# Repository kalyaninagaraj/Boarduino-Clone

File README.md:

# Boarduino Clone 
&nbsp;&nbsp; <br />
This clone-of-a-clone is an adaptation of the breadboard and through-hole parts-friendly [Arduino Uno](https://store.arduino.cc/usa/arduino-uno-rev3), a.k.a. [Boarduino by Lady Ada](https://learn.adafruit.com/boarduino-kits). 

The orginal Boarduino was designed with a ceramic resonator in mind, which isn't available at my local electronics stores. So I redesigned the layout in [Autodesk EAGLE](https://www.autodesk.com/products/eagle) to make space for the more readily available crystal oscillator. 

## Final Product
Check out this [blinking LED demo](https://youtu.be/2WAObtuopfo) for a look at the final (manufactured and assembled) board. 

### A Note On The Microcontroller 
I could only manage to get my hands on a [ATMEGA328-PU](https://www.microchip.com/wwwproducts/en/ATMEGA328), and not the Arduino-supported [ATMEGA328P-PU](https://www.microchip.com/wwwproducts/en/ATMEGA328P), which means bootloading troubles! Of the handful of workarounds that I found on the web, [this one](http://www.crash-bang.com/resource/bootload-atmega328/) helped the most.  

## Resources
Here are links to the original Boarduino, other Boarduino-like products, and some related resources. 
1. [DC and USB Boarduino kits and assembly tutorial by Lada Ada, Adafruit Industries](https://learn.adafruit.com/boarduino-kits). 
2. [Really Bare Bones Board (RBBB) by Modern Device](https://moderndevice.com/product/rbbb-kit/). Their [document on assembly instructions](https://cdn.shopify.com/s/files/1/0038/9582/files/RBBB_Instructions_06.pdf?1260749296) includes a great how-to section for soldering novices.
3. If the purple PCB in the video wasn't enough of a hint, I got the boards fabricated from [OSH Park](https://oshpark.com/)! 

## Design Credit
[@kalyaninagaraj](https://github.com/kalyaninagaraj)

## Hardware License
The design files are made available under [CC BY-SA 3.0](https://creativecommons.org/licenses/by-sa/3.0/).

## Tags
#Open-Source Hardware #Arduino Uno Clone # Boarduino Clone #Adafruit

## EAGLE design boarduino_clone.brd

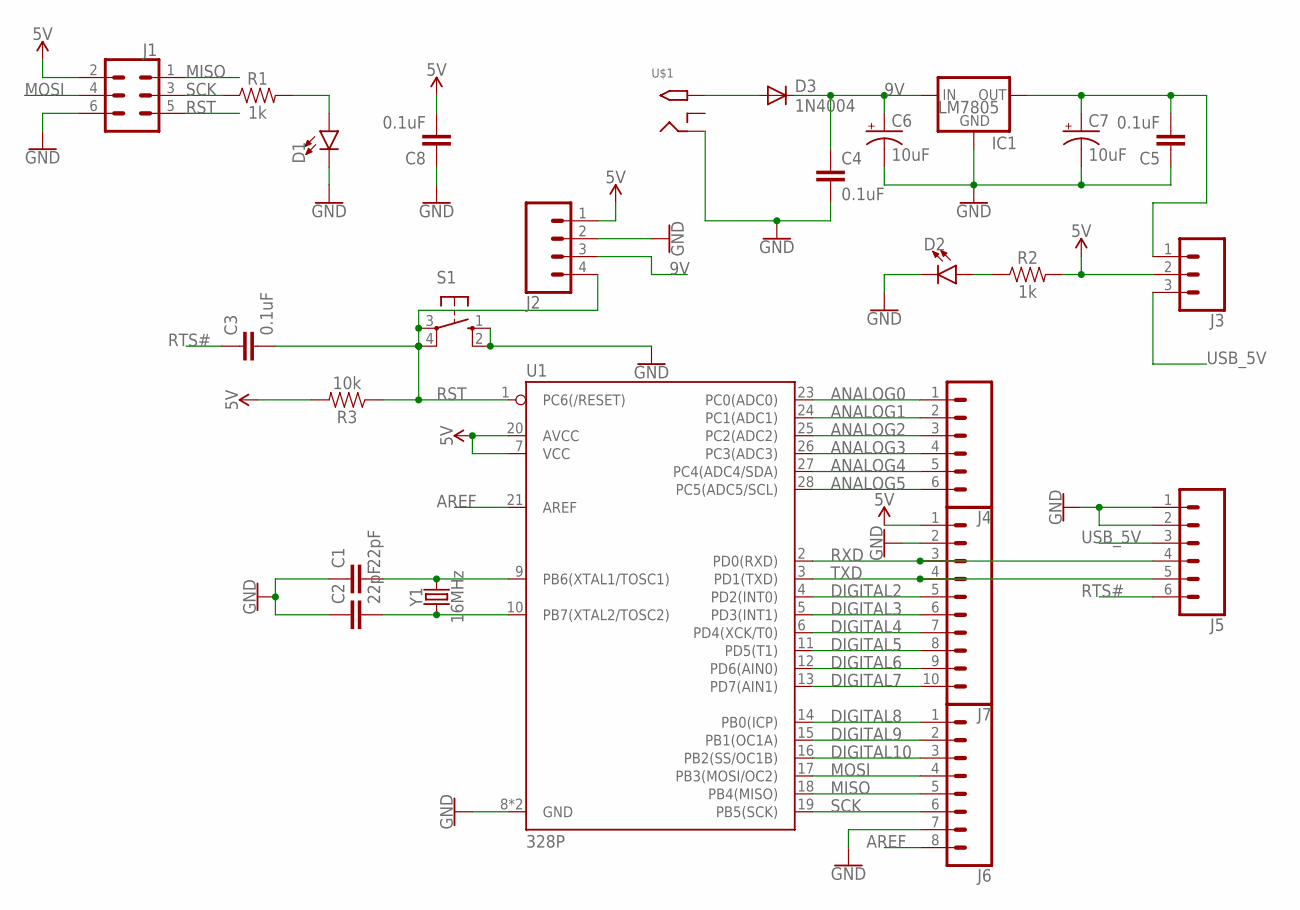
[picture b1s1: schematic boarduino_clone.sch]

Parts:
C1, C2: 22pF; CAP-PTH-2.54
C3, C4, C5, C8: 0.1uF; CAP-PTH-SMALL-KIT
C6, C7: 10uF; CPOL-RADIAL-2.5MM-5MM
D1, D2: LED5MM; LED_5MM
D3: 1N4004; DO41-10
IC1: LM7805; 78XXS
J1: FEMALE 2x3; 2X3
J2: CONN_041X04_NO_SILK; 1X04_NO_SILK
J3: CONN_031X03_NO_SILK; 1X03_NO_SILK
J4, J5: CONN_06NO_SILK_FEMALE_PTH; 1X06_NO_SILK
J6: CONN_08NO_SILK_FEMALE_PTH; 1X08_NO_SILK
J7: CONN_10NO_SILK_PTH_FEMALE; 1X10_NO_SILK
R1, R2: 1k; AXIAL-0.1
R3: 10k; AXIAL-0.1
S1: 10-XX; B3F-10XX
U1: 328P; DIP28
U$1: 2.1MMJACKTHM; PJ-102A
Y1: 16MHz; HC49US

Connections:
5V: C8.2, J1.2, J2.1, J3.2, J7.1, R2.P$2 (2), R3.P$2 (2), U1.7 (VCC), U1.20 (AVCC)
9V: C4.1, C6.1 (+), D3.C, IC1.IN, J2.3
ANALOG0: J4.1, U1.23 (PC0(ADC0))
ANALOG1: J4.2, U1.24 (PC1(ADC1))
ANALOG2: J4.3, U1.25 (PC2(ADC2))
ANALOG3: J4.4, U1.26 (PC3(ADC3))
ANALOG4: J4.5, U1.27 (PC4(ADC4/SDA))
ANALOG5: J4.6, U1.28 (PC5(ADC5/SCL))
AREF: J6.8, U1.21 (AREF)
DIGITAL2: J7.5, U1.4 (PD2(INT0))
DIGITAL3: J7.6, U1.5 (PD3(INT1))
DIGITAL4: J7.7, U1.6 (PD4(XCK/T0))
DIGITAL5: J7.8, U1.11 (PD5(T1))
DIGITAL6: J7.9, U1.12 (PD6(AIN0))
DIGITAL7: J7.10, U1.13 (PD7(AIN1))
DIGITAL8: J6.1, U1.14 (PB0(ICP))
DIGITAL9: J6.2, U1.15 (PB1(OC1A))
DIGITAL10: J6.3, U1.16 (PB2(SS/OC1B))
GND: C1.1, C2.1, C4.2, C5.1, C6.2 (-), C7.2 (-), C8.1, D1.K (C), D2.K (C), IC1.GND, J1.6, J2.2, J5.1, J5.2, J6.7, J7.2, S1.1 (S), S1.2 (S1), U1.8 (GND), U1.22 (GND), U$1.RING
MISO: J1.1, J6.5, U1.18 (PB4(MISO))
MOSI: J1.4, J6.4, U1.17 (PB3(MOSI/OC2))
unnamed: D1.A, R1.P$2 (2)
unnamed: C1.2, U1.9 (PB6(XTAL1/TOSC1)), Y1.2
unnamed: C2.2, U1.10 (PB7(XTAL2/TOSC2)), Y1.1
unnamed: D3.A, U$1.TIP
unnamed: C5.2, C7.1 (+), IC1.OUT, J3.1
unnamed: D2.A, R2.P$1 (1)
RST: C3.2, J1.5, J2.4, R3.P$1 (1), S1.3, S1.4 (P1), U1.1 (PC6(/RESET))
RTS#: C3.1, J5.6
RXD: J5.4, J7.3, U1.2 (PD0(RXD))
SCK: J1.3, J6.6, R1.P$1 (1), U1.19 (PB5(SCK))
TXD: J5.5, J7.4, U1.3 (PD1(TXD))
USB_5V: J3.3, J5.3

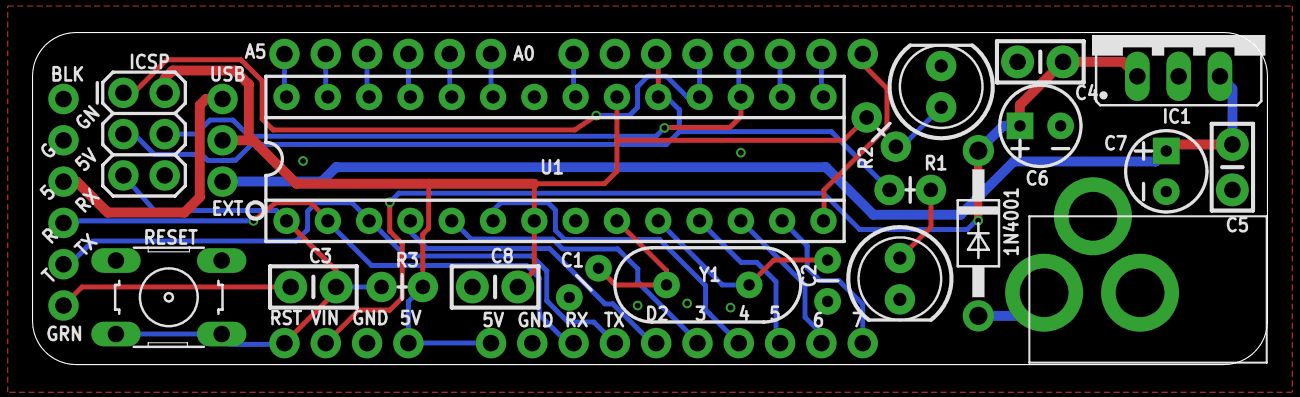
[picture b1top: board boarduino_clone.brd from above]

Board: 2 copper layers, 75.9 x 20.4 mm, 26 parts (0 on the bottom side), 33 nets.

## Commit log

2021-04-08 upload Eagle CAD files
2021-04-08 Upload images and readme
2021-04-20 add YouTube link

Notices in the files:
parts and their libraries:
SparkFun-Capacitors: Licensing: Creative Commons ShareAlike 4.0 International - https://creativecommons.org/licenses/by-sa/4.0
